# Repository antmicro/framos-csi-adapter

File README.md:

# Framos CSI Adapter

Copyright (c) 2022-2025 [Antmicro](https://www.antmicro.com>)

## Overview

This repository contains open hardware design files for an FSA to CSI Adapter.

The board serves as a connector adapter between a [FRAMOS Sensor Module Adapter](https://www.framos.com/en/products/framos-sensor-module-adapter-fsa-22408) (FSA) and a 30-wire I-PEX micro coax cable.

The adapter board is the same size as the FSA and can be stacked with it.
The adapter board can be interfaced with a variety of video processing platforms created by Antmicro using the [Dual I-PEX CSI Interposer](https://github.com/antmicro/dual-ipex-csi-interposer).

## Repository structure

The main repository directory contains KiCad PCB project files, a [LICENSE](LICENSE), and a README.

The remaining files are stored in the following directories:

* `lib` - contains the component libraries
* `doc` - contains the adapter [schematics](doc/framos-csi-adapter.pdf)
* `img` - contains graphics for this README
* `assets` - contains visual assets for showcasing this design on [Open Hardware Portal](https://openhardware.antmicro.com)

## Key features

* MIPI CSI-2 camera interface
* On-board DC-DC converters to power the FSA board and camera module
* I2C bus voltage level translator
* DF40C-60DS connector for [FRAMOS Sensor Module Adapter](https://www.framos.com/en/products/framos-sensor-module-adapter-fsa-22408)
* MSAK24024 Series 30-pin IPEX-type connector

## License

[Apache-2.0](LICENSE)

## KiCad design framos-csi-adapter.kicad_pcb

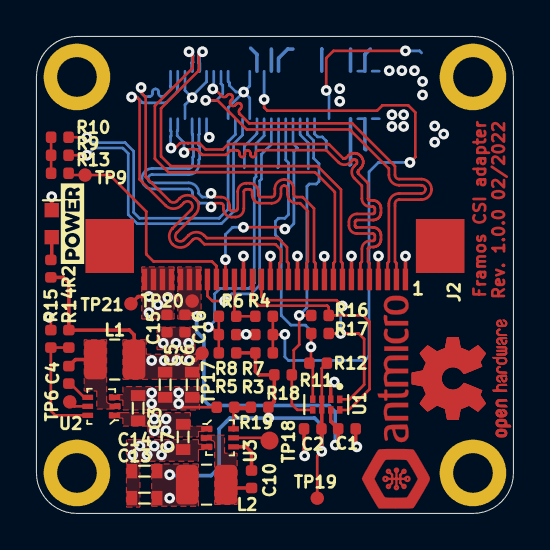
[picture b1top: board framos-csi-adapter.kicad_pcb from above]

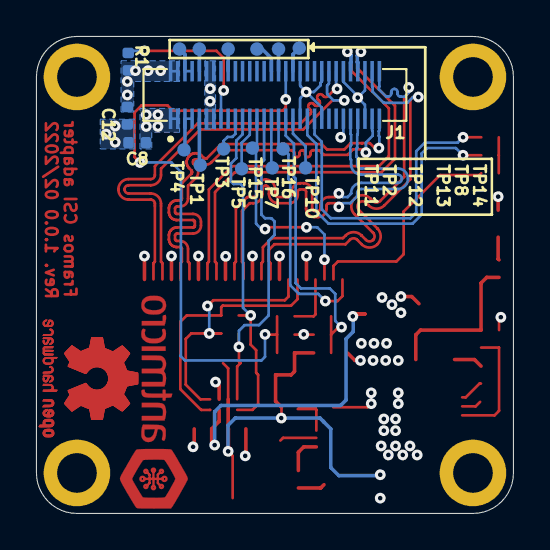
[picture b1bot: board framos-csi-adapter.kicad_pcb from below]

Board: 4 copper layers, 26.5 x 26.5 mm, 68 parts (22 on the bottom side), 50 nets.

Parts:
C1, C2, C4, C8, C10, C12, C15, C16: C_100n_0402; 0402-cap
C3, C5, C6, C7, C13, C14: C_22u_0603; 0603-cap
D1: KP-1608CGCK; LED_0603
J1: DF40C-60DS-0.4V(51); DF40C-60DS-0.4V51
J2: MSAK24025P30
L1, L2: 74479887222C; L_1008_2520Metric
MP1, MP2, MP3, MP4: PCB_Mount_Hole_2.2_4.5; mounting-hole-2.2mm
N2: antmicro_logo; antmicro-logo_scaled_12mm
R1, R3, R5: R_100k_0402; 0402-res
R2: R_330R_0402; 0402-res
R4, R6, R15, R19: R_10k_0402; 0402-res
R7, R8: R_12k_0402; 0402-res
R9, R10, R13, R16, R17: R_0R_0402; 0402-res
R11, R12: R_2k2_0402; 0402-res
R14: R_37k4_0402; 0402-res
R18: R_12k4_0402; 0402-res
TP1, TP2, TP3, TP4, TP5, TP6, TP7, TP8, TP9, TP10, TP11, TP12, TP13, TP14, TP15, TP16, TP17, TP19, TP20, TP21: TP_SMD_0_75MM; Testpoint_smd_0_75mm
TP18: TP_SMD1MM; Testpoint_smd_1mm
U1: NTS0102GT; PSON50P100X195X50-8N
U2, U3: AP62301Z6-7; SOT-563
kibuzzard-621A77E1: G***; label

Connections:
1V8_CAM: C2.1, C12.1, C13.1, C14.1, J1.2, J1.4, L2.2, R1.1, R3.2, R5.1, R11.1, R12.1, R18.1, TP19.1, U1.3, U1.6
3V3FFC: C1.1, C16.1, J2.24, J2.25, J2.26, TP20.1, U1.7
3V8_CAM: C5.1, C6.1, C8.1, J1.1, J1.3, L1.2, R2.1, R14.1, TP17.1
5V0_SYS: C3.1, C7.1, C15.1, J2.27, J2.28, J2.29, J2.30, TP21.1, U2.1, U3.1
/AUX_ANA: J1.5, J1.7, TP4.1
/AUX_DIG: J1.6, J1.8, TP11.1
/AUX_IF: J1.9, TP1.1
/AUX_V: J1.10, TP2.1
/INCK: J1.39, R9.2
/MCLK1: J1.41, R10.2
/PW_EN_0: J1.33, R5.2, R6.2, R8.2
/PW_EN_1: J1.34, R3.1, R4.2, R7.1
/SDO: J1.18, TP12.1
/SLAMODE1: J1.35, TP10.1
/SLAMODE2: J1.36, TP14.1
/TENABLE: J1.30, TP13.1
/TOUT: J1.32, TP8.1
/XCE: J1.23, TP5.1
/XCLR: J1.15, R1.2
/XHS: J1.29, TP7.1
/XMASTER: J1.19, TP3.1
CAM_SCL_1V8: J1.21, R11.2, R16.1, U1.5
CAM_SCL_3V3: J2.18, R16.2, U1.8
CAM_SDA_1V8: J1.27, R12.2, R17.1, U1.4
CAM_SDA_3V3: J2.17, R17.2, U1.1
CSI_CAM_CLK: J2.22, R13.1, TP9.1
CSI_CAM_EN: J2.20, R4.1, R6.1
CSI_CAM_XTRIG: J1.31, J2.23, TP16.1
CSI_CAM_XVS: J1.25, J2.21, TP15.1
CSI_CLK_N: J1.60, J2.14
CSI_CLK_P: J1.58, J2.15
CSI_D0_N: J1.51, J2.11
CSI_D0_P: J1.53, J2.12
CSI_D1_N: J1.52, J2.8
CSI_D1_P: J1.54, J2.9
CSI_D2_N: J1.59, J2.5
CSI_D2_P: J1.57, J2.6
CSI_D3_N: J1.48, J2.2
CSI_D3_P: J1.46, J2.3
GND: C1.2, C2.2, C3.2, C5.2, C6.2, C7.2, C8.2, C12.2, C13.2, C14.2, C15.2, C16.2, D1.2, J1.11, J1.12, J1.13, J1.14, J1.37, J1.38, J1.43, J1.44, J1.49, J1.50, J1.55, J1.56, J2.1, J2.4, J2.7, J2.10, J2.13, J2.16, J2.19, R7.2, R8.1, R15.2, R19.2, U1.2, U2.3, U3.3
unnamed: C4.1, L1.1, U2.2
unnamed: C4.2, U2.4
unnamed: C10.1, L2.1, U3.2
unnamed: C10.2, U3.4
unnamed: D1.1, R2.2
unnamed: R9.1, R10.1, R13.2
unnamed: R14.2, R15.1, U2.6
unnamed: R18.2, R19.1, U3.6
unnamed: TP6.1, U2.5
unnamed: TP18.1, U3.5

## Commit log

2022-01-21 Initial commit - Add PCB design
2022-01-21 Move R1 to top
2022-02-14 Add 3V8 and 1V8 DC/DC to the schematic
2022-02-21 Add 4-line CSI support - update pinout
2022-02-25 Move power supply sections on PCB
2022-02-27 Tweak FB resistors, change L1 and L2 to smaller size
2022-07-28 Add i-pex 30pin plug
2022-07-28 Changed voltage translator to XSON8 package. Crossed P and N signals on D2 and D3 lanes
2022-07-28 Added TP silkscreen map
2022-07-28 Adjust position of passives around U1
2022-07-28 Fixed diff traces impedance
2022-07-28 Update DF40C-60DS-0.4V51 footprint
2022-07-28 Layout, tunning
2022-07-28 Add CI
2022-07-28 Adjust position of the bottom TP labels
2022-07-28 Bump revision to 1.1.0
2022-07-28 Revert PN to DF40C-60DS-0.4V(51)
2022-07-28 Migrate to KiCad 6. Add LICENSE and README. Correct OSHW logo footprint
2022-10-13 Cleanup
2022-10-13 Update README, add photo
2022-10-13 README: fix image path
2022-10-13 Add PDF Schematic
2022-10-19 README: mention matching accessory
2022-10-19 Notes added by 'git notes add'
2023-02-08 Minor README review
2023-03-21 updated FRAMOS branding on H1 and FSA
    FRAMOS in all caps, FRAMOS with 1 registered trademark on site page when tied to products (FSA) per brand styleguide.
2023-10-16 Introduce component standardization
2023-10-16 Bump revision date
2023-10-16 Add OHP assets
2024-01-31 [#54543] Migrate project to KiCad7
2024-01-31 [#54543] Loclib
2024-01-31 [#54543] Update schematic PDF
2024-03-20 [#56796] Fix lib references
2024-03-22 Upload assets
2024-03-26 [#56796] Loclib
2024-03-26 [#56796] Update revision & date
2024-03-28 [#56796] Small PCB fixes, DNP marking
2024-05-27 [#60063] Add si assets
2025-04-23 [#74509] Update EMS results
2025-04-23 [#60063] Update SI assets
2025-04-23 Migrate to KiCad 8
2025-04-23 [#74670] Perform DNP check
2025-04-23 Fix Stackup
